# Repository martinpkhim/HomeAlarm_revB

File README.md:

# HomeAlarm_revB
Repository for the second revision of the HomeAlarm project

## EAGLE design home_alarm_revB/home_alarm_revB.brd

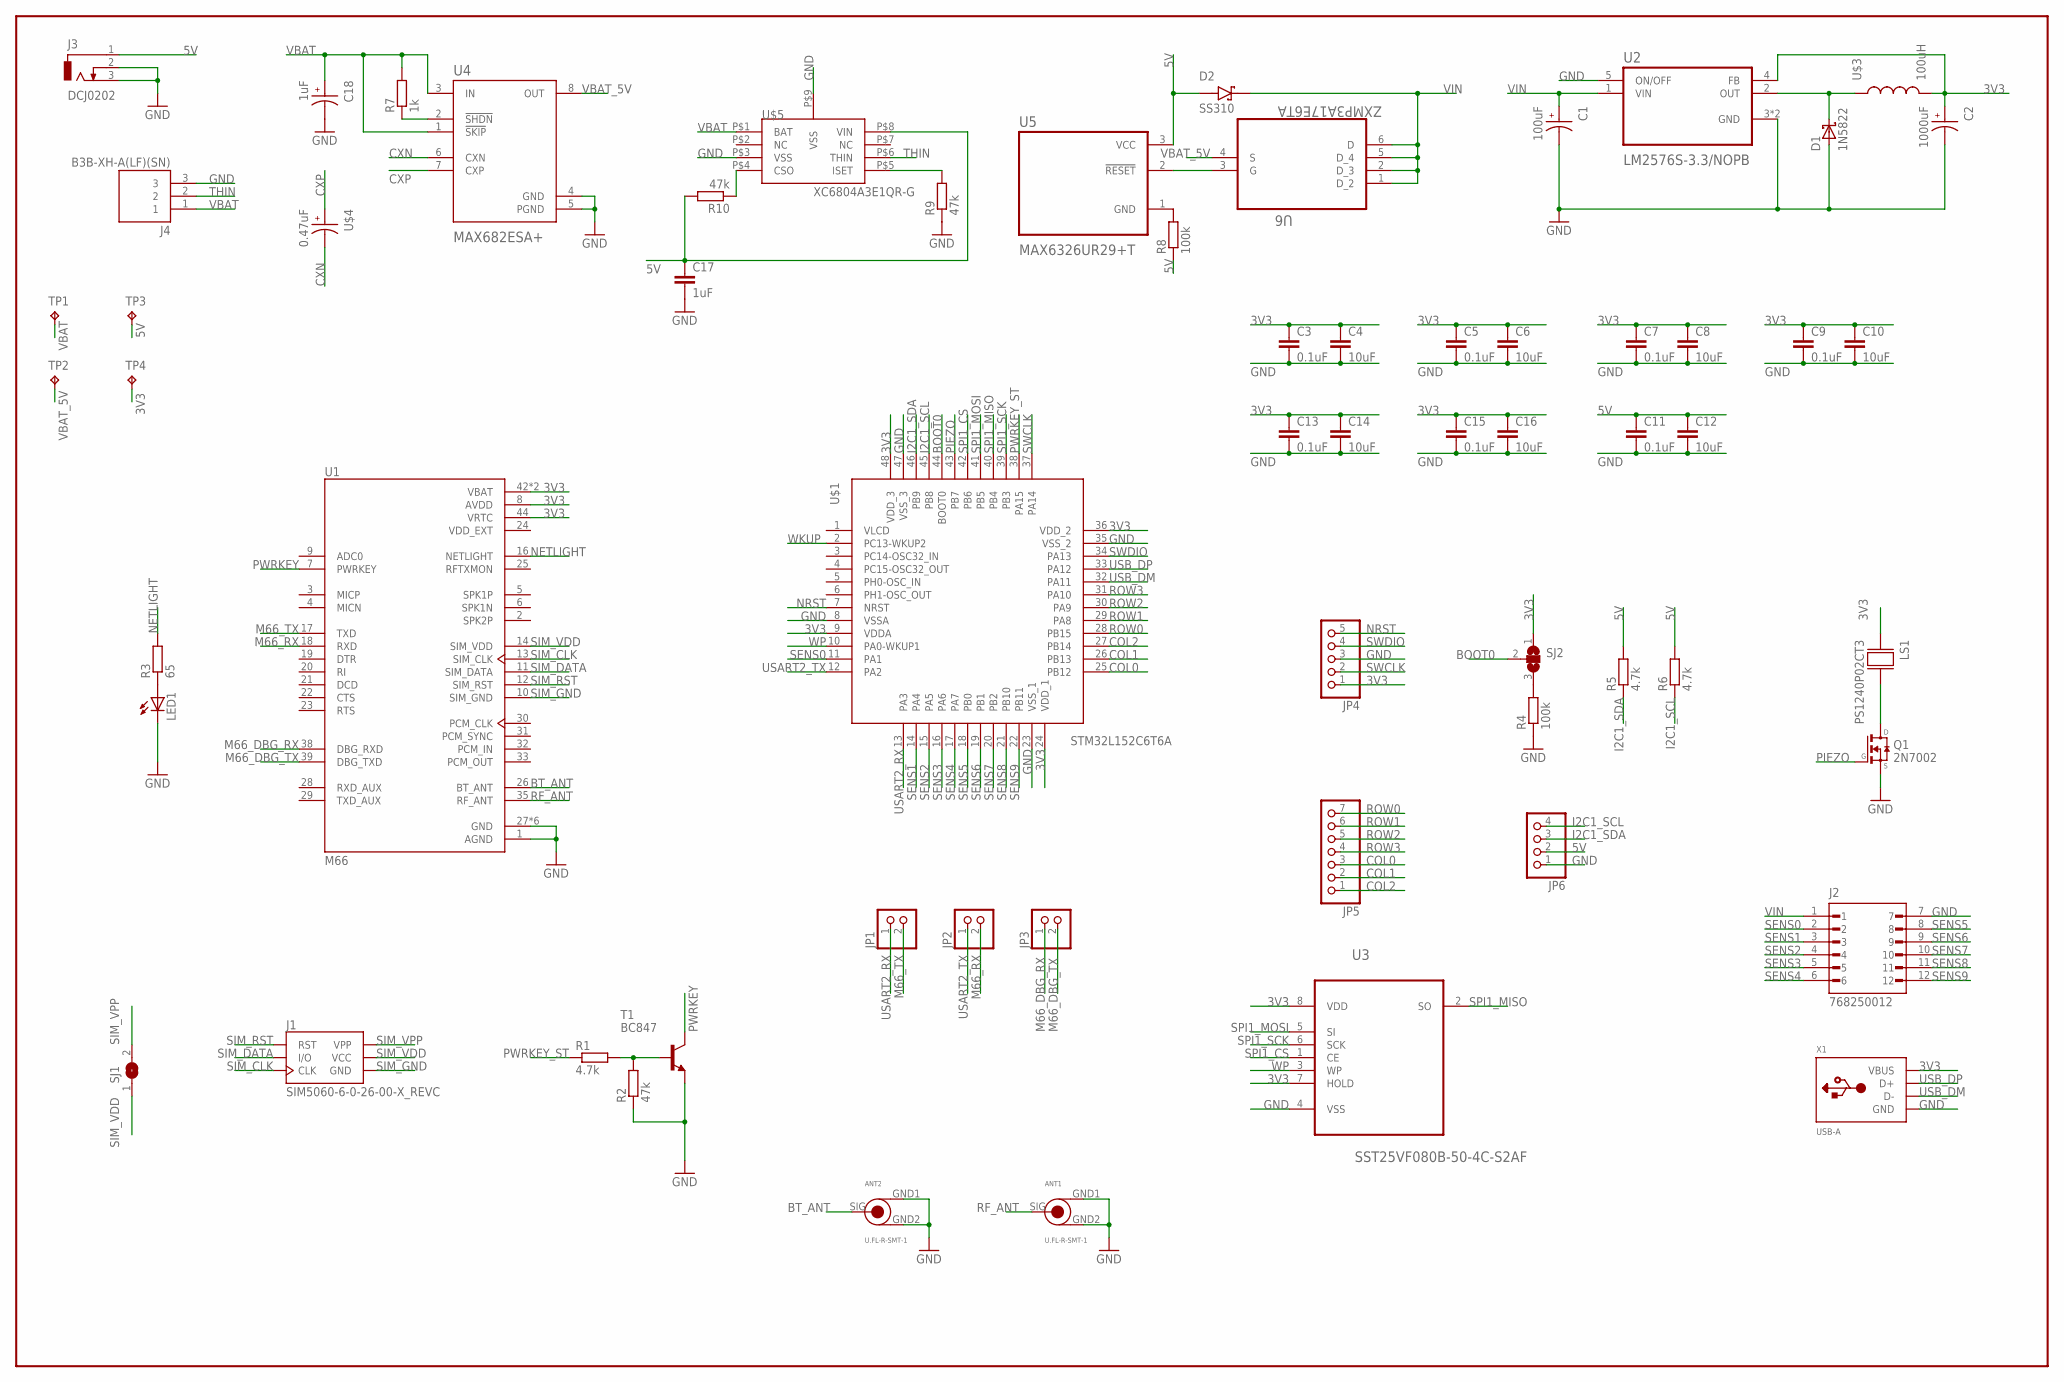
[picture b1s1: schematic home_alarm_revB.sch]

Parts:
ANT1, ANT2: U.FL-R-SMT-1
C1: 100uF; CAP_EEEFP1C101AV
C2: 1000uF; CAP_EEEFK1C102SV
C3, C5, C7, C9, C11, C13, C15: 0.1uF; C0805
C4, C6, C8, C10, C12, C14, C16: 10uF; C0805
C17: 1uF; C0805
C18: 1uF; CAP_EEE1HA010NR
D1: 1N5822; DIOAD2120W130L950D530P
D2: SS310; DIOM6859X262N
J1: SIM5060-6-0-26-00-X_REVC; GCT_SIM5060-6-0-26-00-X_REVC
J2: 768250012; MOLEX_768250012
J3: DCJ0202
J4: B3B-XH-A(LF)(SN); JST_B3B-XH-A(LF)(SN)
JP1, JP2, JP3: PINHD-1X2; 1X02
JP4: PINHD-1X5; 1X05
JP5: PINHD-1X7; 1X07
JP6: PINHD-1X4; 1X04
LED1: LEDCHIPLED_0603; CHIPLED_0603
LS1: PS1240P02CT3; XDCR_PS1240P02CT3
Q1: 2N7002; SOT23
R1, R5, R6: 4.7k; R0805
R2, R9, R10: 47k; R0805
R3: 65; R0805
R4, R8: 100k; R0805
R7: 1k; R0805
SJ1: SJ
SJ2: SJ2W; SJ_2
T1: BC847; SOT23
TP1, TP2, TP3, TP4: TPB1,27; B1,27
U1: M66; XCVR_M66
U2: LM2576S-3.3/NOPB; VREG_TPS79625KTTR
U3: SST25VF080B-50-4C-S2AF; SOIC127P790X216-8N
U4: MAX682ESA+; SOIC127P600X175-8N
U5: MAX6326UR29+T; SOT95P237X112-3N
U6: ZXMP3A17E6TA; SOT95P280X145-6N
U$1: STM32L152C6T6A
U$3: 100uH; MSS1210-104KED
U$4: 0.47uF; 865230640004
U$5: XC6804A3E1QR-G
X1: USB-A; MOLEX_480371000

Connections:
3V3: C2.1, C3.1, C4.1, C5.1, C6.1, C7.1, C8.1, C9.1, C10.1, C13.1, C14.1, C15.1, C16.1, JP4.1, LS1.1, SJ2.1, TP4.TP, U1.8 (AVDD), U1.42 (VBAT), U1.43 (VBAT), U1.44 (VRTC), U2.4 (FB), U3.7 (HOLD), U3.8 (VDD), U$1.9 (VDDA), U$1.24 (VDD_1), U$1.36 (VDD_2), U$1.48 (VDD_3), U$3.P$2 (2), X1.1 (VBUS)
5V: C11.1, C12.1, C17.1, D2.A, J3.1, JP6.2, R5.2, R6.2, R8.1, R10.2, TP3.TP, U5.3 (VCC), U$5.P$8 (VIN)
BOOT0: SJ2.2, U$1.44 (BOOT0)
BT_ANT: ANT2.SIG, U1.26 (BT_ANT)
COL0: JP5.3, U$1.25 (PB12)
COL1: JP5.2, U$1.26 (PB13)
COL2: JP5.1, U$1.27 (PB14)
CXN: U4.6 (CXN), U$4.2
CXP: U4.7 (CXP), U$4.1
GND: ANT1.GND1, ANT1.GND2, ANT2.GND1, ANT2.GND2, C1.2, C2.2, C3.2, C4.2, C5.2, C6.2, C7.2, C8.2, C9.2, C10.2, C11.2, C12.2, C13.2, C14.2, C15.2, C16.2, C17.2, C18.2, D1.A, J2.7, J3.2, J3.3, J4.3, JP4.3, JP6.1, LED1.C, Q1.2 (S), R2.1, R4.1, R9.1, T1.2 (E), U1.1 (AGND), U1.27 (GND), U1.34 (GND), U1.36 (GND), U1.37 (GND), U1.40 (GND), U1.41 (GND), U2.3 (GND), U2.5 (ON/OFF), U2.6 (GND), U3.4 (VSS), U4.4 (GND), U4.5 (PGND), U$1.8 (VSSA), U$1.23 (VSS_1), U$1.35 (VSS_2), U$1.47 (VSS_3), U$5.P$3 (VSS), U$5.P$9 (VSS), X1.4 (GND)
I2C1_SCL: JP6.4, R6.1, U$1.45 (PB8)
I2C1_SDA: JP6.3, R5.1, U$1.46 (PB9)
M66_DBG_RX: JP3.1, U1.38 (DBG_RXD)
M66_DBG_TX: JP3.2, U1.39 (DBG_TXD)
M66_RX: JP2.2, U1.18 (RXD)
M66_TX: JP1.2, U1.17 (TXD)
unnamed: LS1.2, Q1.3 (D)
unnamed: R7.1, U4.2 (!SHDN)
unnamed: R8.2, U5.1 (GND)
unnamed: R9.2, U$5.P$5 (ISET)
unnamed: U5.2 (!RESET), U6.3 (G)
unnamed: R10.1, U$5.P$4 (CSO)
unnamed: D1.C, U2.2 (OUT), U$3.P$1 (1)
unnamed: R1.2, R2.2, T1.1 (B)
unnamed: LED1.A, R3.1
unnamed: R4.2, SJ2.3
NETLIGHT: R3.2, U1.16 (NETLIGHT)
NRST: JP4.5, U$1.7 (NRST)
PIEZO: Q1.1 (G), U$1.43 (PB7)
PWRKEY: T1.3 (C), U1.7 (PWRKEY)
PWRKEY_ST: R1.1, U$1.38 (PA15)
RF_ANT: ANT1.SIG, U1.35 (RF_ANT)
ROW0: JP5.7, U$1.28 (PB15)
ROW1: JP5.6, U$1.29 (PA8)
ROW2: JP5.5, U$1.30 (PA9)
ROW3: JP5.4, U$1.31 (PA10)
SENS0: J2.2, U$1.11 (PA1)
SENS1: J2.3, U$1.14 (PA4)
SENS2: J2.4, U$1.15 (PA5)
SENS3: J2.5, U$1.16 (PA6)
SENS4: J2.6, U$1.17 (PA7)
SENS5: J2.8, U$1.18 (PB0)
SENS6: J2.9, U$1.19 (PB1)
SENS7: J2.10, U$1.20 (PB2)
SENS8: J2.11, U$1.21 (PB10)
SENS9: J2.12, U$1.22 (PB11)
SIM_CLK: J1.C3 (CLK), U1.13 (SIM_CLK)
SIM_DATA: J1.C7 (I/O), U1.11 (SIM_DATA)
SIM_GND: J1.C5 (GND), U1.10 (SIM_GND)
SIM_RST: J1.C2 (RST), U1.12 (SIM_RST)
SIM_VDD: J1.C1 (VCC), SJ1.1, U1.14 (SIM_VDD)
SIM_VPP: J1.C6 (VPP), SJ1.2
SPI1_CS: U3.1 (CE), U$1.42 (PB6)
SPI1_MISO: U3.2 (SO), U$1.40 (PB4)
SPI1_MOSI: U3.5 (SI), U$1.41 (PB5)
SPI1_SCK: U3.6 (SCK), U$1.39 (PB3)
SWCLK: JP4.2, U$1.37 (PA14)
SWDIO: JP4.4, U$1.34 (PA13)
THIN: J4.2, U$5.P$6 (THIN)
USART2_RX: JP1.1, U$1.13 (PA3)
USART2_TX: JP2.1, U$1.12 (PA2)
USB_DM: U$1.32 (PA11), X1.2 (D-)
USB_DP: U$1.33 (PA12), X1.3 (D+)
VBAT: C18.1, J4.1, R7.2, TP1.TP, U4.1 (!SKIP), U4.3 (IN), U$5.P$1 (BAT)
VBAT_5V: TP2.TP, U4.8 (OUT), U6.4 (S)
VDD_EXT: U1.24 (VDD_EXT)
VIN: C1.1, D2.C (K), J2.1, U2.1 (VIN), U6.1 (D_2), U6.2 (D_3), U6.5 (D_4), U6.6 (D)
WKUP: U$1.2 (PC13-WKUP2)
WP: U3.3 (WP), U$1.10 (PA0-WKUP1)

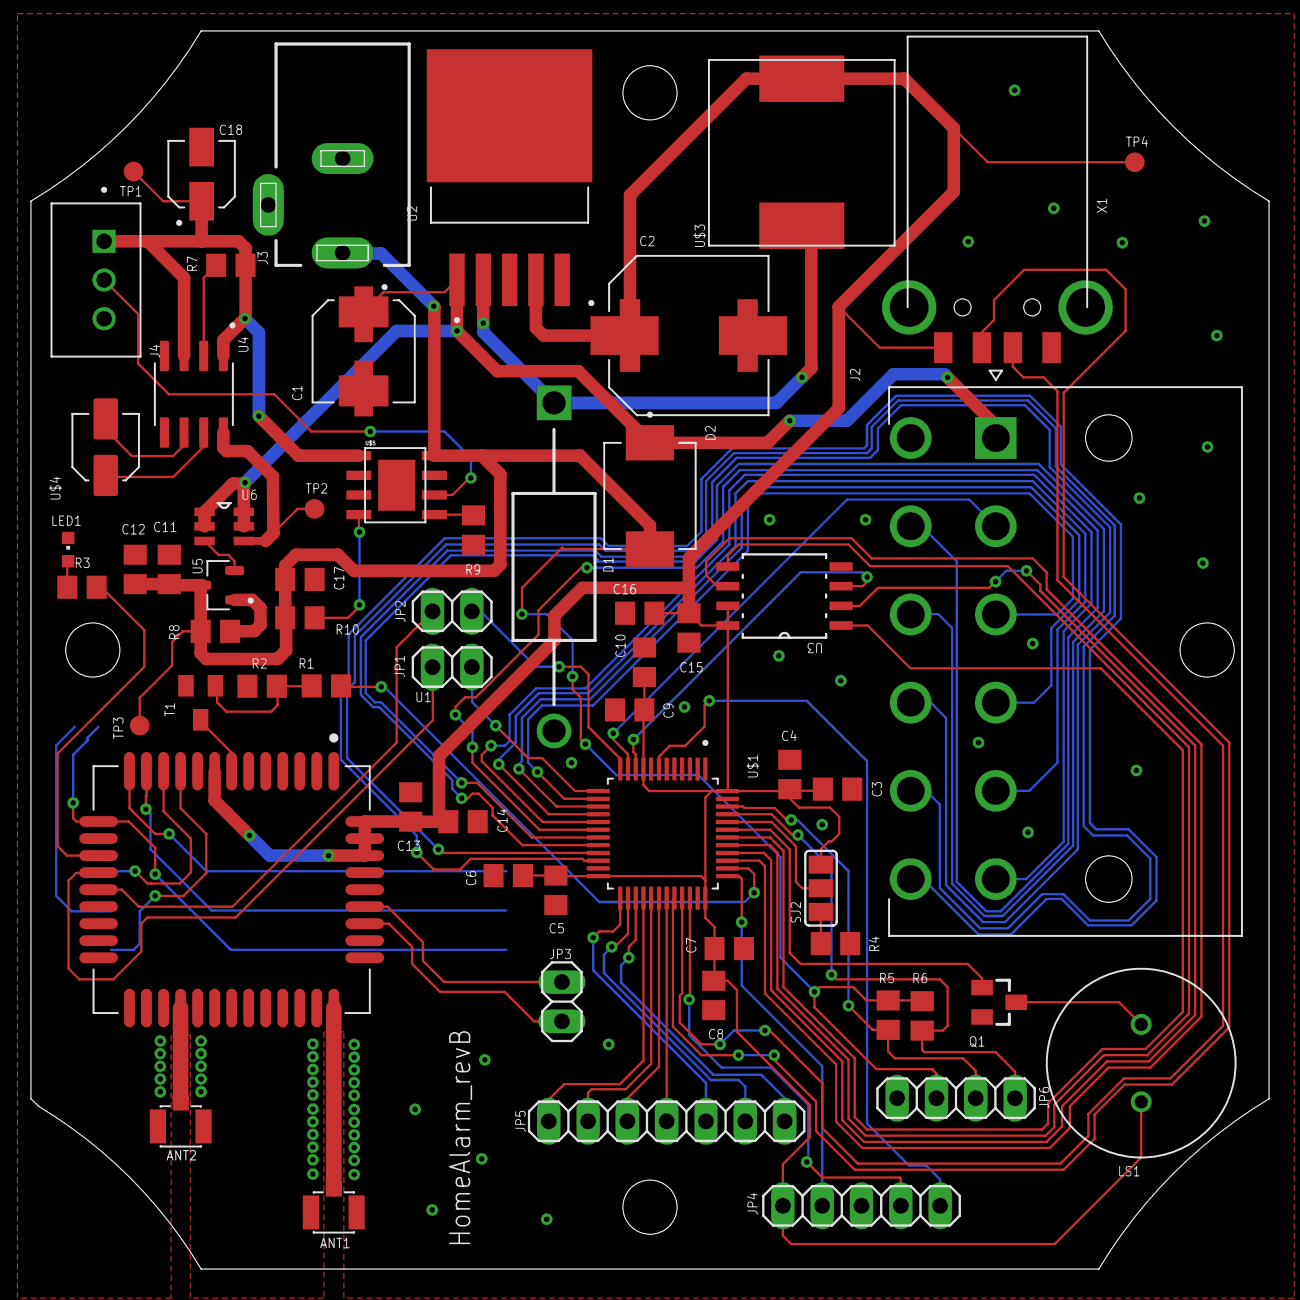
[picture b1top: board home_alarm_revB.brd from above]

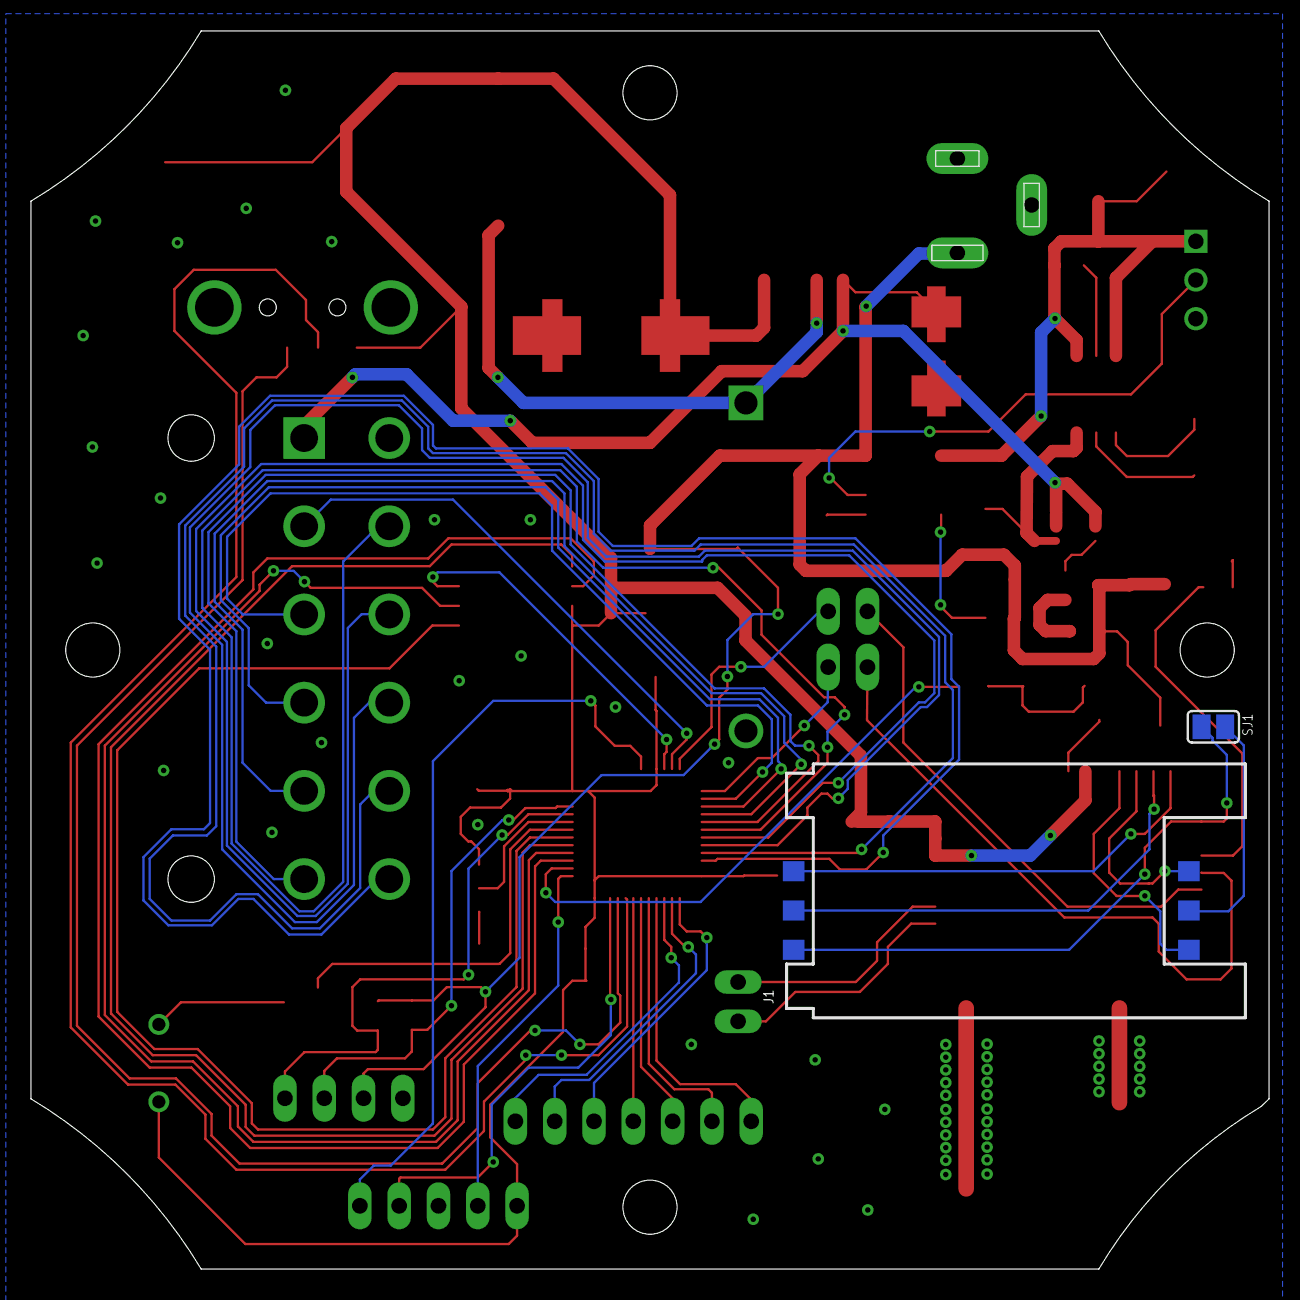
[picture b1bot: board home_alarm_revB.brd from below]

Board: 2 copper layers, 80.0 x 80.0 mm, 63 parts (2 on the bottom side), 67 nets.

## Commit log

2022-03-20 Initial commit containing the finished pcb design
